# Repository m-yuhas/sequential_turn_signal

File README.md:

# Sequential Turn Signal
[中文指南](https://github.com/m-yuhas/sequential_turn_signal/blob/master/doc/读我档案.md)

[Documentación en español](https://github.com/m-yuhas/sequential_turn_signal/blob/master/doc/LÉAME.md)

[Documentation en français](https://github.com/m-yuhas/sequential_turn_signal/blob/master/doc/LISEZ-MOI.md)

## Introduction
On modern vehicles sequential turn signals are rapidly increasing in popularity.
A sequential turn signal is a turn signal which is divided into multiple
segments that illuminate in some dynamic pattern when the signal is activated.
While this functionality comes built in to many modern vehicles, this project
seeks to provide a simple method to introduce this functionality to classic cars
without having to replace the existing turn signal lights.  The software and
hardware are configured by default for a vehicle with three independent rear
turn signal lamps on each side of the vehicle, but can be adapted for other
configurations if needed.

If you plan to install this system on your vehicle, please read this entire
guide and understand what tools and skills you will need to complete this
project before beginning.  A high level of automotive and electronics experience
is recommended as this system has not yet been tested in an operating
environment.  Furthermore, it was designed for a specific vehicle and
modifications may be required to use it in another.

Please check the local regulations regarding modifications to vehicles before
starting.  This system will also introduce sequential behavior when the break
lights first illuminate, which may or may not be legal in your jurisdiction.
Additionally please understand the risks to yourself, your vehicle, and those
with whom you share the road.  These include, but are not limited to
electrocution, fire, messing up your vehicle's wiring harness, and ending up
with a vehicle with no working turn signals or break lights.  Proceed at your
own risk.

## Building the System
This system is composed of three components: a PCB with the microcontroller and
electronics; firmware, which runs on the microcontroller; and an enclosure to
offer some protection for the functional components of the system.  Each of the
sections below contains more details about each component, how to build it, and
some possible modifications.

### PCB

The schematic and PCB were created with
[EAGLE](https://www.autodesk.com/products/eagle/overview?term=1-YEAR). The
project can be loaded from the files in this repository's pcb folder.  Here are
the steps to build:
1. Use EAGLE to export Gerber files from the main.brd file.  You can follow
  [these instructions](https://www.autodesk.com/products/eagle/blog/gerber-nc-drill-pcb-manufacturing-basics-1/) from Autodesk.
2. Find a PCB manufacturer and send the Gerber files and Excellon drill files
  for manufacture.
3. You should receive a blank PCB from the manufacturer.  All the components
  were selected as through-hole to make home assembly easier.  You will need to
  purchase all the parts by model number as shown on the schematic.
4. Solder the components to the PCB.

Some things to consider:
1. This PCB intercepts the right and left turn signal lines and splits each into
  three signals lines for each individual lamp.  Assuming 30 Watt brake lamps,
  some of these traces will be passing up to 2.5 Amps, so if possible it is
  recommended to widen some of these traces to reduce resistance and mitigate
  the risk of thermal failure of the PCB.
2. The connectors for power, ground, input, and output are not automotive grade.
  They were selected as screw-in connectors to make debugging easier.  These
  should be replaced with proper connectors if possible.
3. The PCB layout contains sufficient space for a toroidal inductor for the
  switched mode power supply.  If you plan on making your own inductor, you can
  calculate the number of turns required using [this guide](http://www.nessengr.com/technical-data/toroid-inductor-formulas-and-calculator/).
  Remember to choose a wire thick enough to support up to 1 Amp.

### Software

The software component is composed of two finite state machines running on an
MSP430 microcontroller.  There is one FSM for each turn signal: when the input
signal line goes high, the FSM begins traversing through the output pattern
vectors with transitions based on times.  Once the input signal line goes low,
the FSM is reset.

The software was created with TI's [Code Composer Studio](https://www.ti.com/tool/CCSTUDIO).
You can load the project with the files in this repository's firmware folder.
Here are the steps to compile the firmware and load it on the PCB:
1. Buy an [MSP430 programmer](https://www.ti.com/tool/MSP-FET).
2. Open the Code Composer Studio project in this repository's firmware folder.
3. Connect the programmer to the debug header on the PCB.  The PCB's debug
  header is designed to communicate with the programmer using SBW and UART.
4. Follow the instructions in the [Code Composer Studio manual](https://www.ti.com/lit/ug/spru509h/spru509h.pdf)
  to flash the device.
5. When power is introduced on the PCB's 12 V power supply input, the MSP430
  should boot.  You can verify functionality by supplying 12 V to either left or
  right signal inputs and monitoring the voltages on the output pins.

Some things to consider:
1. You can define custom patterns using the macros at the top of the main.c file
2. You can speed up or slow down the sequential pattern by changing the
  definition of TIMER_RESOLUTION_TICKS in main.c
3. The version of the MSP430 used in this project only has one 8-bit port.  If
  your vehicle has more than six individual lamps (3 per side) that need to be
  controlled, you will need to select a different microcontroller and redesign
  the PCB.

### Enclosure

The enclosure was designed using [OpenSCAD](https://openscad.org/).  This is not
a weatherproof design and the goal is to provide a minimum level of protection
for the PCB.  As such, it is recommended to install the enclosure in the
interior of the vehicle.

The enclosure CAD drawings are meant as a rough guide.  You can machine your own
metal enclosure based on the the drawings or convert them to STL files and 3D
print the pieces.  If the enclosure is 3D printed, please ensure that a plastic
is used which can handle the thermal extremes that can be found inside a
vehicle.

## Installing the System

The system has the following connections with the vehicle's wiring:
* **Power** - 12 V from the vehicle's low voltage battery.  Ideally this should
  come from a line that is high when the system is needed and low when the
  vehicle is parked for long durations.  This is because the microcontroller
  will be running anytime voltage is supplied on this input and could drain the
  battery if the vehicle is parked for a long time.  
* **Ground** - Vehicle ground; this can be connected to the vehicle chassis.
* **Right signal in** - Vehicle's original 12 V line to the right turn signal.
* **Left signal in** - Vehicle's original 12V line to the left turn signal.
* **Right signal out 1** - Connection between the system and the rear inner
  right turn signal lamp.
* **Right signal out 2** - Connection between the system and the rear center
  right turn signal lamp.
* **Right signal out 3** - Connection between the system and the rear outer
  right turn signal lamp.
* **Left signal out 1** - Connection between the system and the rear inner left
  turn signal lamp.
* **Left signal out 2** - Connection between the system and the rear center left
  turn signal lamp.
* **Left signal out 3** - Connection between the system and the rear outer left
  turn signal lamp.

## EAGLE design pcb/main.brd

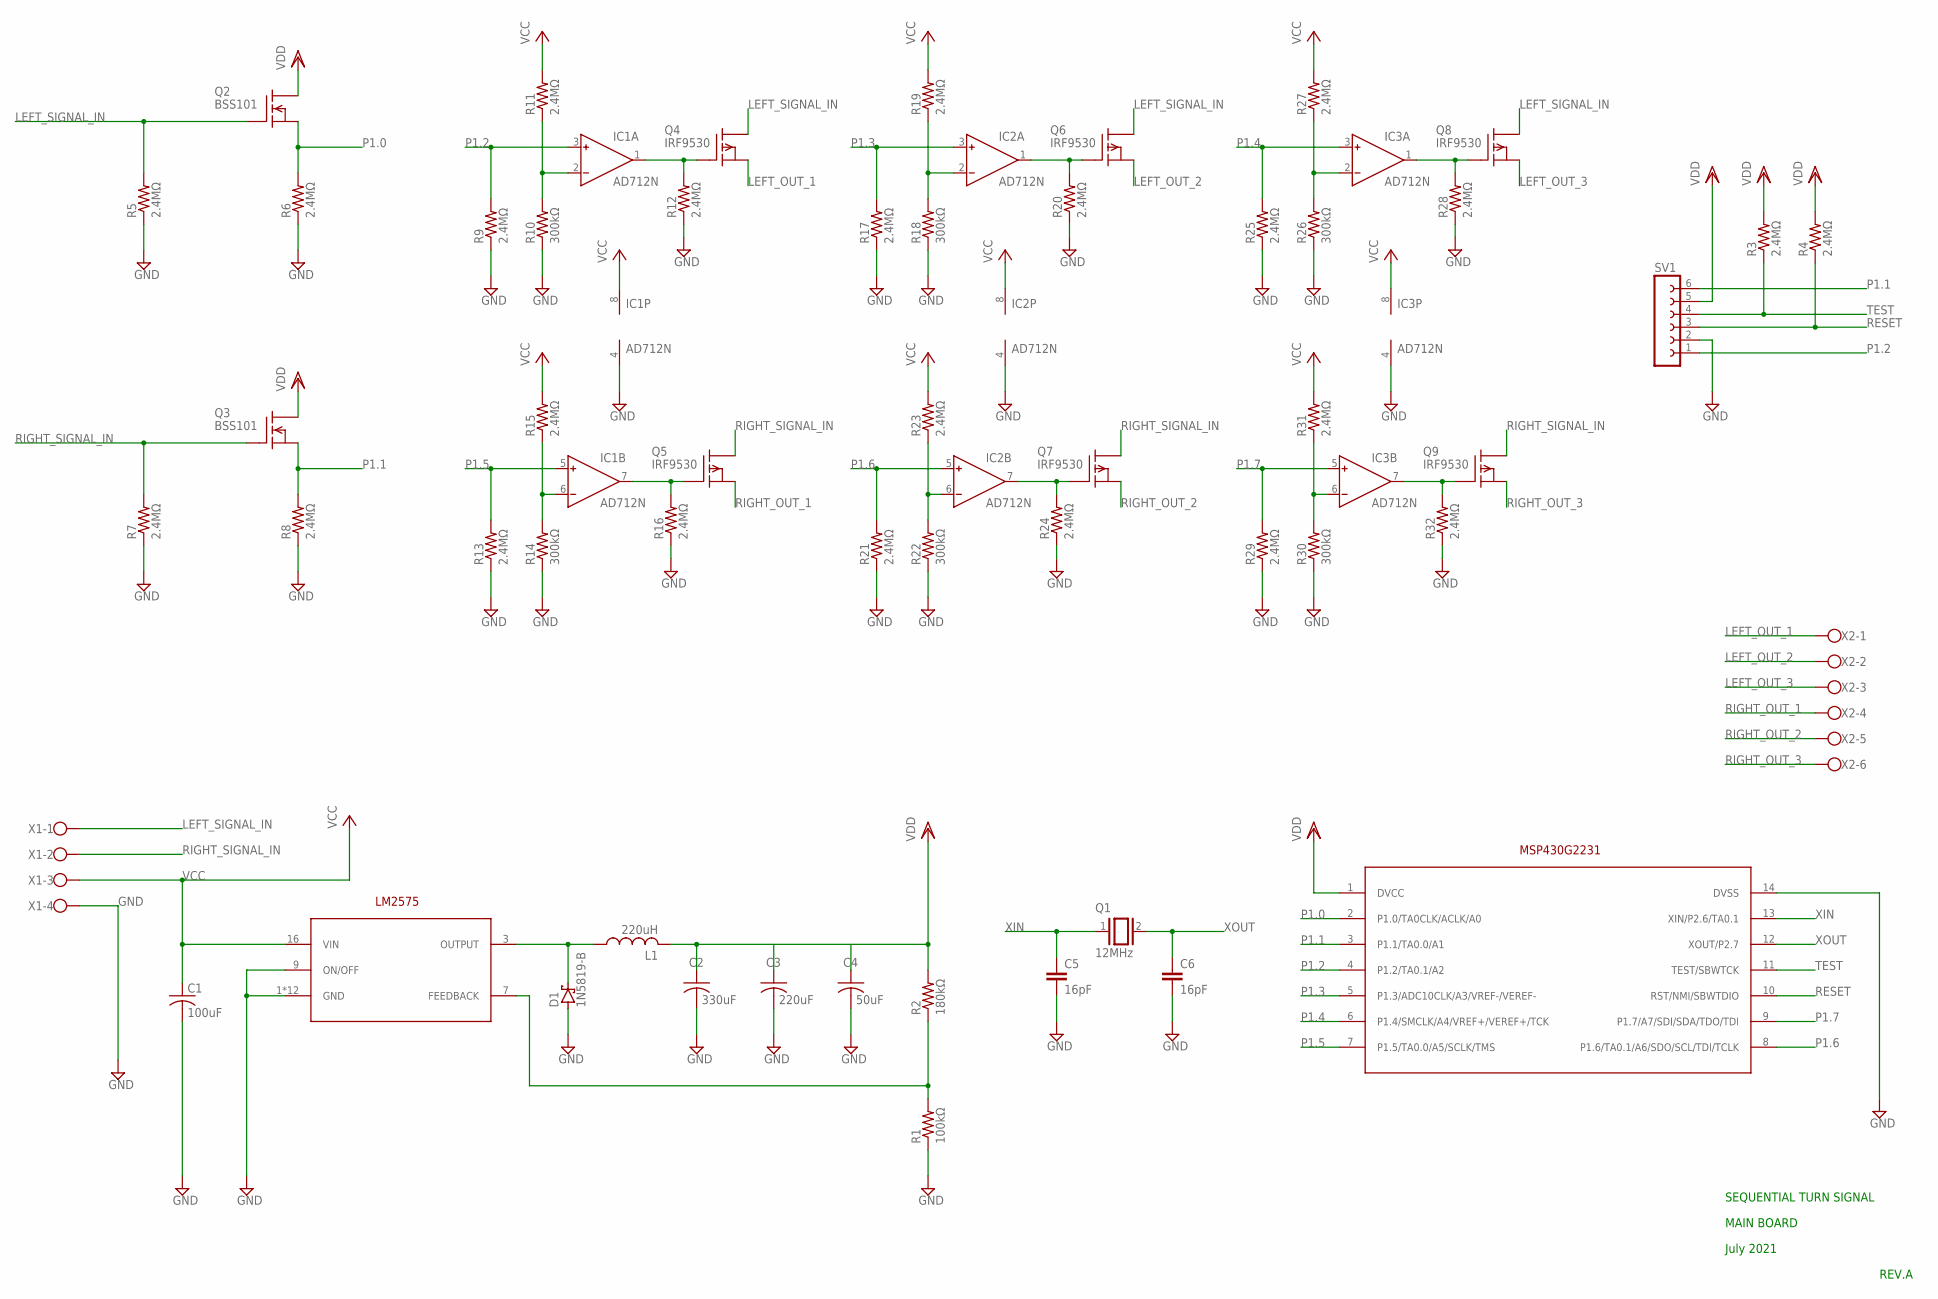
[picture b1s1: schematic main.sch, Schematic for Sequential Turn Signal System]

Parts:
C1: 100uF; C025-050X050
C2: 330uF; C025-050X050
C3: 220uF; C025-050X050
C4: 50uF; C025-050X050
C5, C6: 16pF; C025-024X044
D1: 1N5819-B; DO41-7.6
IC1, IC2, IC3: AD712N; DIL08
L1: 220uH; 6000-XXXX-RC
Q1: 12MHz; Q
Q2, Q3: BSS101; TO92
Q4, Q5, Q6, Q7, Q8, Q9: IRF9530; TO220
R1: 100kΩ; 0207/12
R2: 180kΩ; 0207/12
R3, R4, R5, R6, R7, R8, R9, R11, R12, R13, R15, R16, R17, R19, R20, R21, R23, R24, R25, R27, R28, R29, R31, R32: 2.4MΩ; 0207/12
R10, R14, R18, R22, R26, R30: 300kΩ; 0207/12
SV1: FE06-1; FE06
U$1: MSP430G2231PDIP14; DIP762W53P254L1969H508Q14B
U$2: LM2575PDIP16; DIP762W53P254L1969H508Q16B
X1: W237-4
X2: W237-6

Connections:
GND: C1.2, C2.2, C3.2, C4.2, C5.2, C6.2, D1.A, IC1.4 (V-), IC2.4 (V-), IC3.4 (V-), R1.1, R5.1, R6.1, R7.1, R8.1, R9.1, R10.1, R12.1, R13.1, R14.1, R16.1, R17.1, R18.1, R20.1, R21.1, R22.1, R24.1, R25.1, R26.1, R28.1, R29.1, R30.1, R32.1, SV1.2, U$1.14 (DVSS), U$2.1 (GND), U$2.2 (GND), U$2.4 (GND), U$2.5 (GND), U$2.6 (GND), U$2.8 (GND), U$2.9 (ON/OFF), U$2.10 (GND), U$2.11 (GND), U$2.12 (GND), U$2.13 (GND), U$2.14 (GND), U$2.15 (GND), X1.4
LEFT_OUT_1: Q4.3 (S), X2.1
LEFT_OUT_2: Q6.3 (S), X2.2
LEFT_OUT_3: Q8.3 (S), X2.3
LEFT_SIGNAL_IN: Q2.2 (G), Q4.2 (D), Q6.2 (D), Q8.2 (D), R5.2, X1.1
unnamed: D1.C, L1.1, U$2.3 (OUTPUT)
unnamed: R1.2, R2.1, U$2.7 (FEEDBACK)
unnamed: IC1.6 (IN-), R14.2, R15.1
unnamed: IC1.7 (OUT), Q5.1 (G), R16.2
unnamed: IC1.1 (OUT), Q4.1 (G), R12.2
unnamed: IC1.2 (IN-), R10.2, R11.1
unnamed: IC2.6 (IN-), R22.2, R23.1
unnamed: IC2.7 (OUT), Q7.1 (G), R24.2
unnamed: IC2.1 (OUT), Q6.1 (G), R20.2
unnamed: IC2.2 (IN-), R18.2, R19.1
unnamed: IC3.6 (IN-), R30.2, R31.1
unnamed: IC3.7 (OUT), Q9.1 (G), R32.2
unnamed: IC3.1 (OUT), Q8.1 (G), R28.2
unnamed: IC3.2 (IN-), R26.2, R27.1
P1.0: Q2.1 (S), R6.2, U$1.2 (P1.0/TA0CLK/ACLK/A0)
P1.1: Q3.1 (S), R8.2, SV1.6, U$1.3 (P1.1/TA0.0/A1)
P1.2: IC1.3 (IN+), R9.2, SV1.1, U$1.4 (P1.2/TA0.1/A2)
P1.3: IC2.3 (IN+), R17.2, U$1.5 (P1.3/ADC10CLK/A3/VREF-/VEREF-)
P1.4: IC3.3 (IN+), R25.2, U$1.6 (P1.4/SMCLK/A4/VREF+/VEREF+/TCK)
P1.5: IC1.5 (IN+), R13.2, U$1.7 (P1.5/TA0.0/A5/SCLK/TMS)
P1.6: IC2.5 (IN+), R21.2, U$1.8 (P1.6/TA0.1/A6/SDO/SCL/TDI/TCLK)
P1.7: IC3.5 (IN+), R29.2, U$1.9 (P1.7/A7/SDI/SDA/TDO/TDI)
RESET: R4.1, SV1.3, U$1.10 (RST/NMI/SBWTDIO)
RIGHT_OUT_1: Q5.3 (S), X2.4
RIGHT_OUT_2: Q7.3 (S), X2.5
RIGHT_OUT_3: Q9.3 (S), X2.6
RIGHT_SIGNAL_IN: Q3.2 (G), Q5.2 (D), Q7.2 (D), Q9.2 (D), R7.2, X1.2
TEST: R3.1, SV1.4, U$1.11 (TEST/SBWTCK)
VCC: C1.1, IC1.8 (V+), IC2.8 (V+), IC3.8 (V+), R11.2, R15.2, R19.2, R23.2, R27.2, R31.2, U$2.16 (VIN), X1.3
VDD: C2.1, L1.2, Q2.3 (D), Q3.3 (D), R2.2, R3.2, R4.2, SV1.5, U$1.1 (DVCC)
VDD1: C3.1
VDD2: C4.1
XIN: C5.1, Q1.1, U$1.13 (XIN/P2.6/TA0.1)
XOUT: C6.1, Q1.2, U$1.12 (XOUT/P2.7)

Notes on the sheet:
SEQUENTIAL TURN SIGNAL
MAIN BOARD
July 2021
REV.A

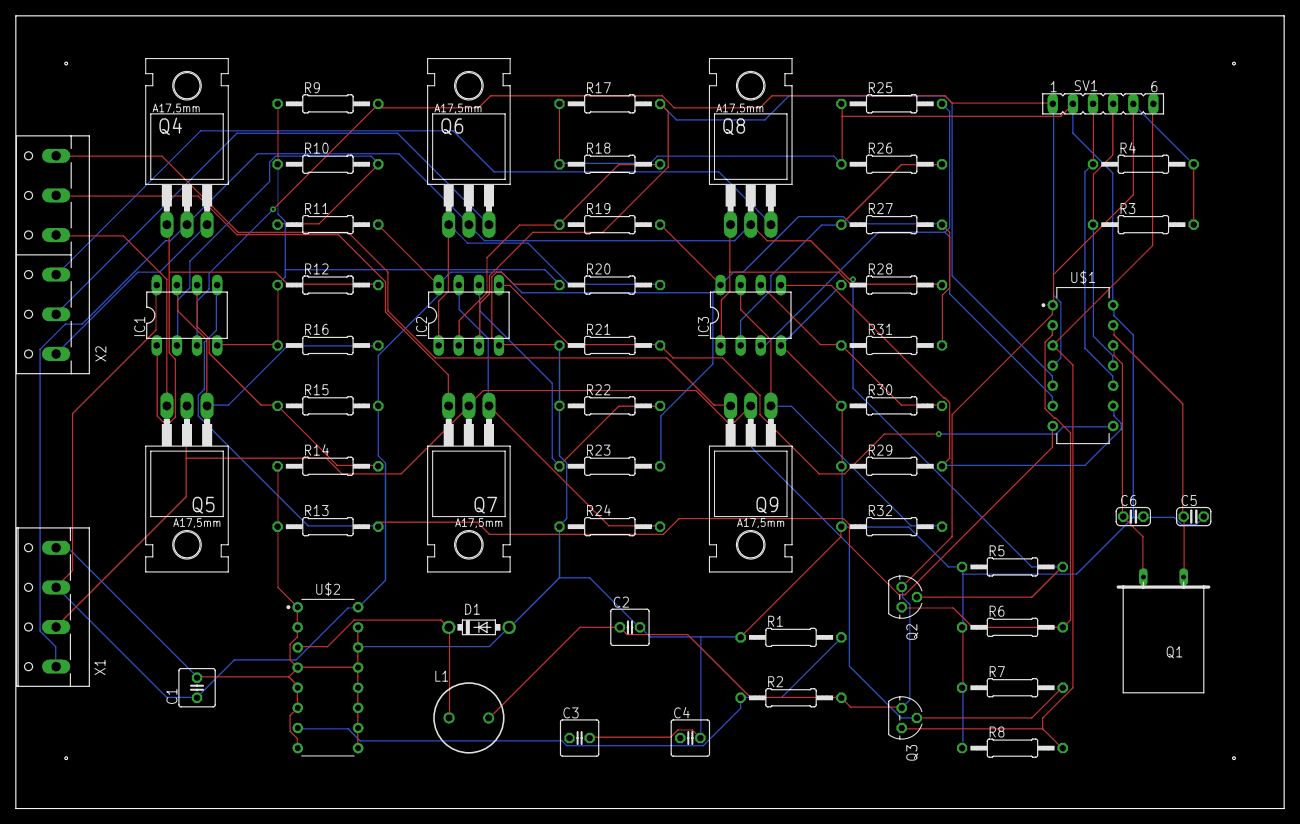
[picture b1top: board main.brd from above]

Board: 2 copper layers, 160.0 x 100.0 mm, 57 parts (0 on the bottom side), 37 nets.

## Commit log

2017-01-30 Initial Commit
    Starting on Code
2017-02-12 Committing Code Changes
    Working on State Machine, currently failing linking
2017-02-13 Committing Changes
    May need to reorganize state machine
2017-02-18 Committing Changes
2017-04-03 Changing Turn Signal Behaviour
    Now Signal Flashes Sequentially Within One Normal Blink
2017-04-05 Playing with Cadsoft Eagle
    Playing with Cadsoft Eagle
2017-04-13 Refactored Code
    Now State Machines Run in Main, with interrupts passing info via globals
2017-09-19 Committing Left and Right Turn Signal Code
2017-09-19 deleting old files
2017-09-20 Adding watchdog timer for safety
2019-04-01 Moving schematic to top level
2021-06-28 uploading finished schematic and board layout
2021-06-28 removing duplicate files
2021-06-28 Create LICENSE
2021-06-30 Adding 1st SCAD model
2021-07-01 drafts of enclosure
2021-07-02 finishing touches on CAD models
2021-07-02 Readme update
2021-07-17 Doc update
2021-07-17 Testing image urls
2021-07-17 Trying URLs again
2021-07-17 Starting French doc translation
2021-07-19 Finished French translation
2021-07-26 Documentation update
